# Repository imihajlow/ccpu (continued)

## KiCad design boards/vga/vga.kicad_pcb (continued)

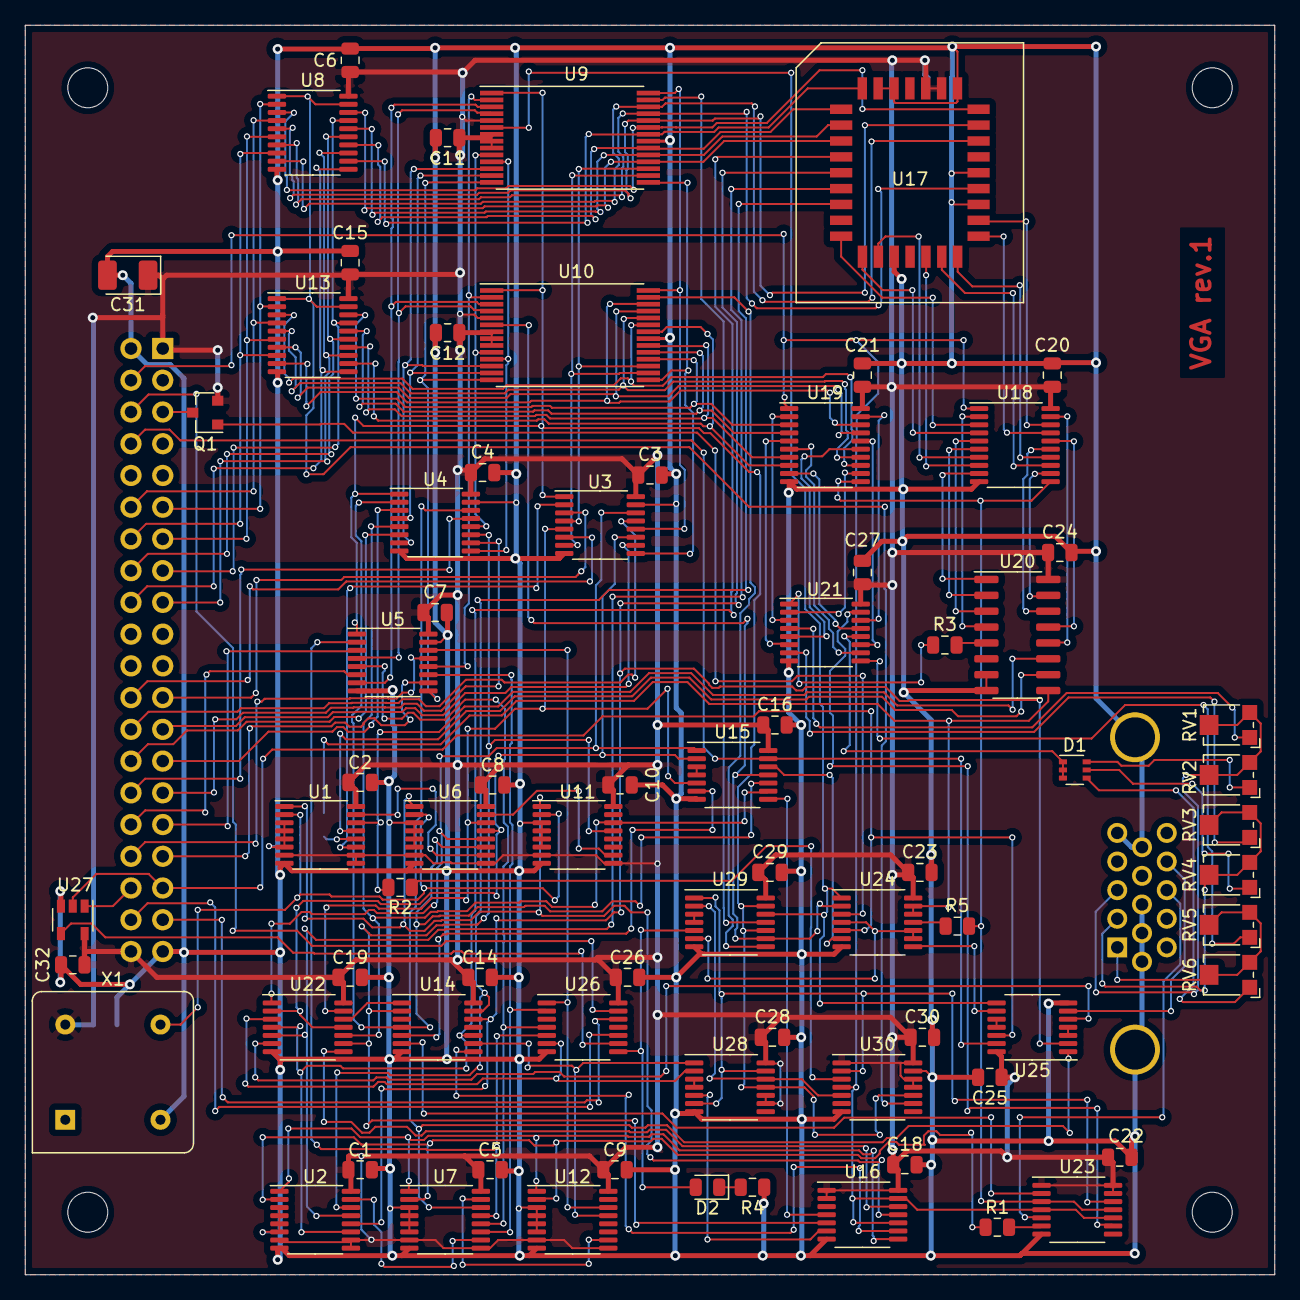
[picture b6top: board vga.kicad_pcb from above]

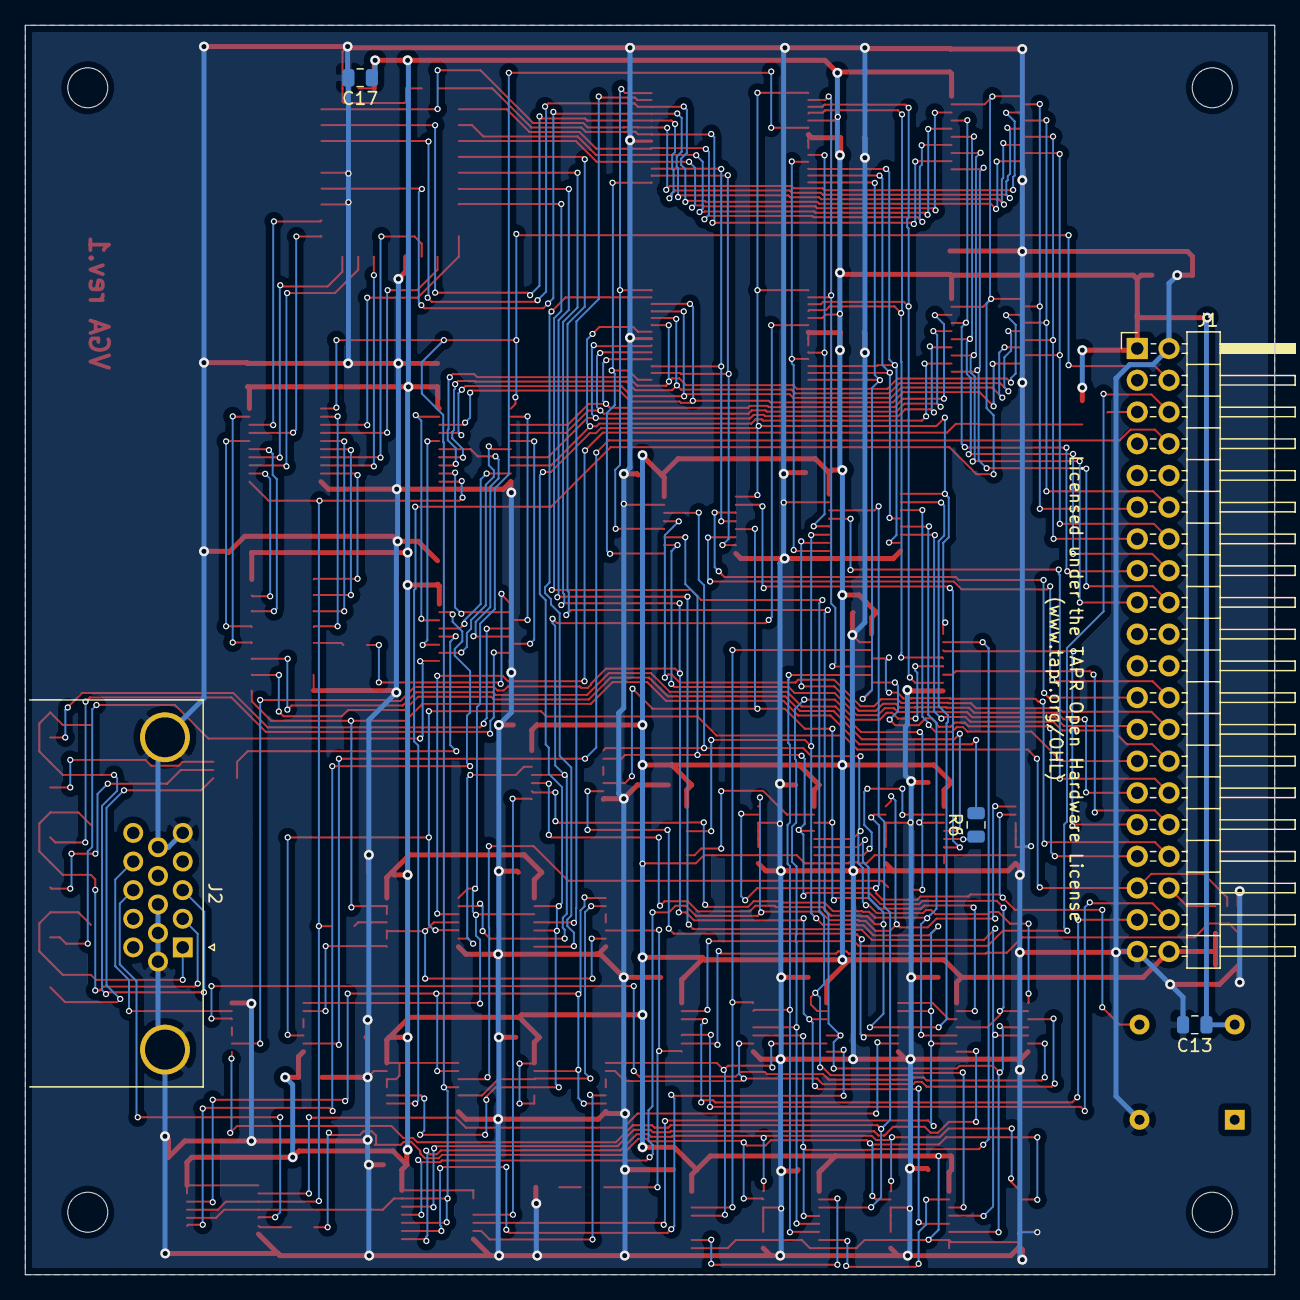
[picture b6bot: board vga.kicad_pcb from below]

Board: 2 copper layers, 100.0 x 100.0 mm, 84 parts (5 on the bottom side), 159 nets.

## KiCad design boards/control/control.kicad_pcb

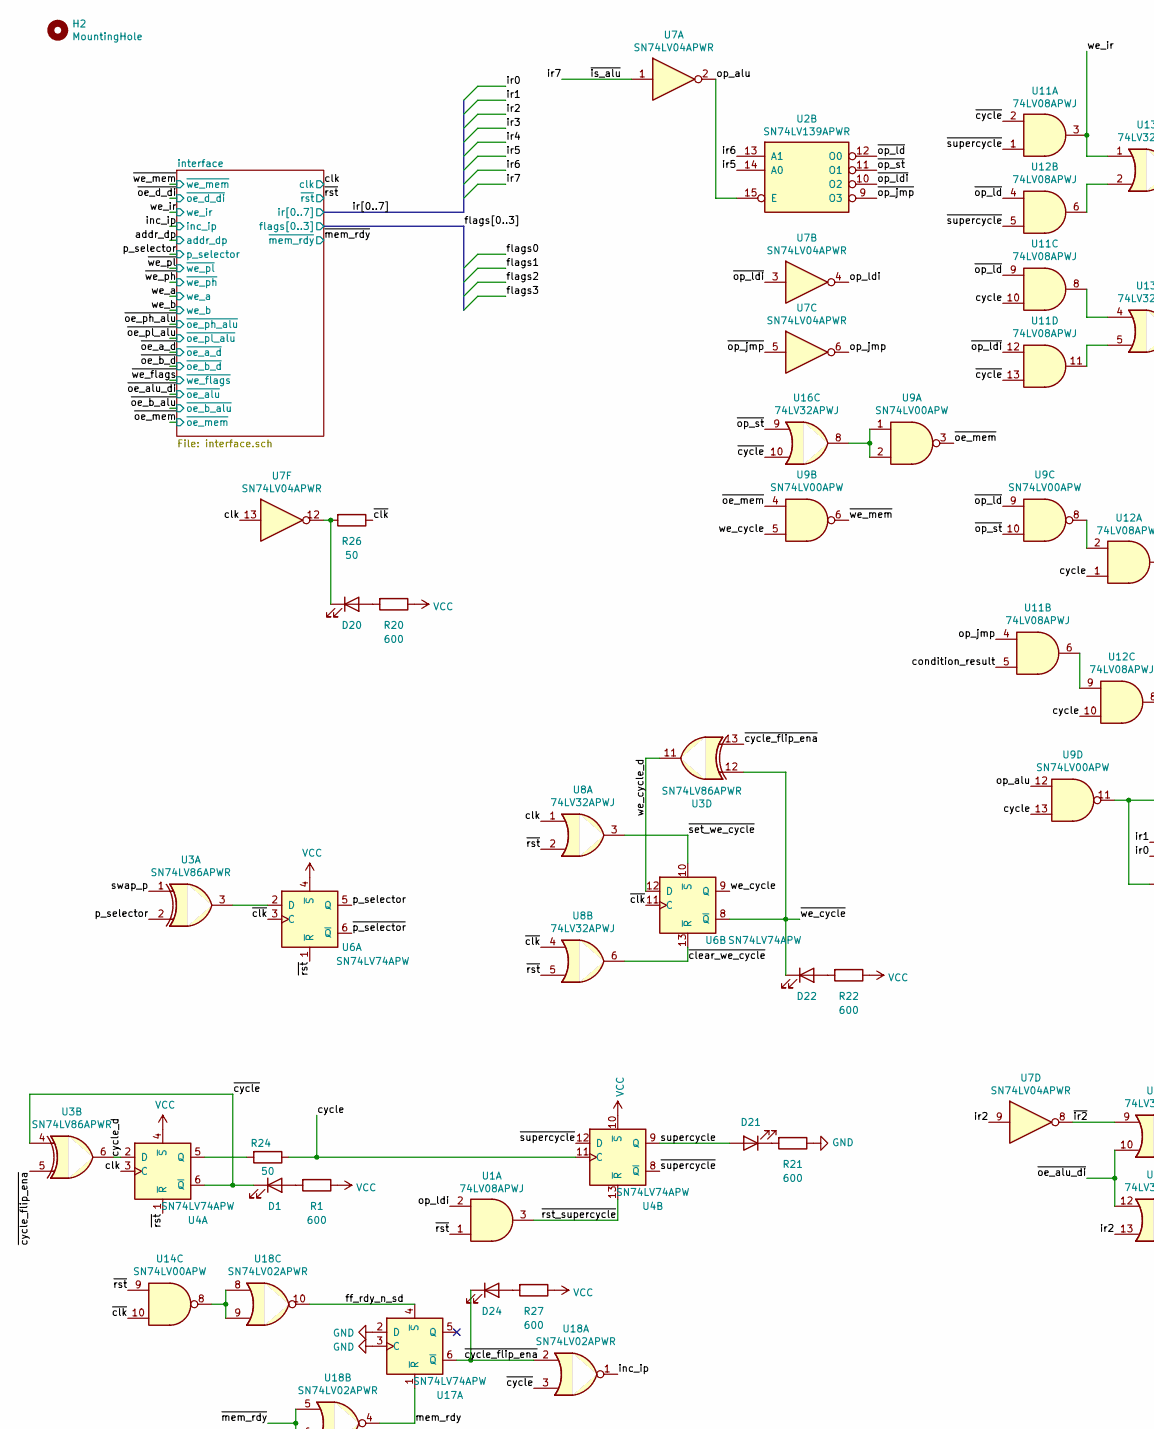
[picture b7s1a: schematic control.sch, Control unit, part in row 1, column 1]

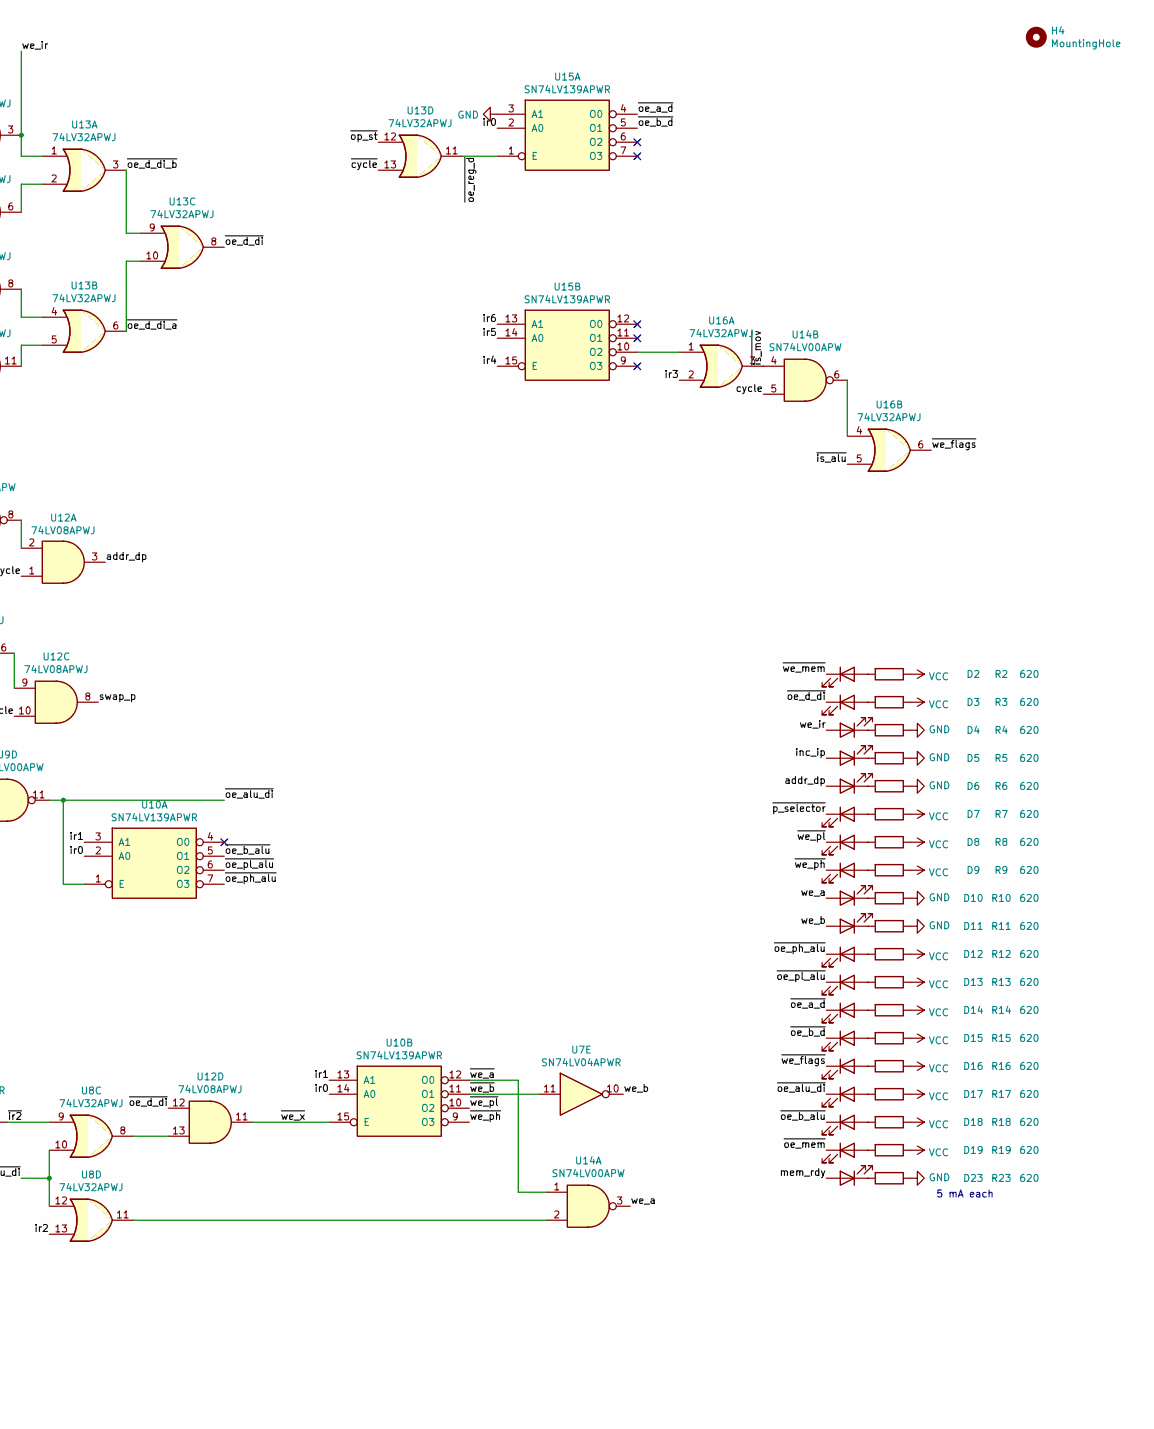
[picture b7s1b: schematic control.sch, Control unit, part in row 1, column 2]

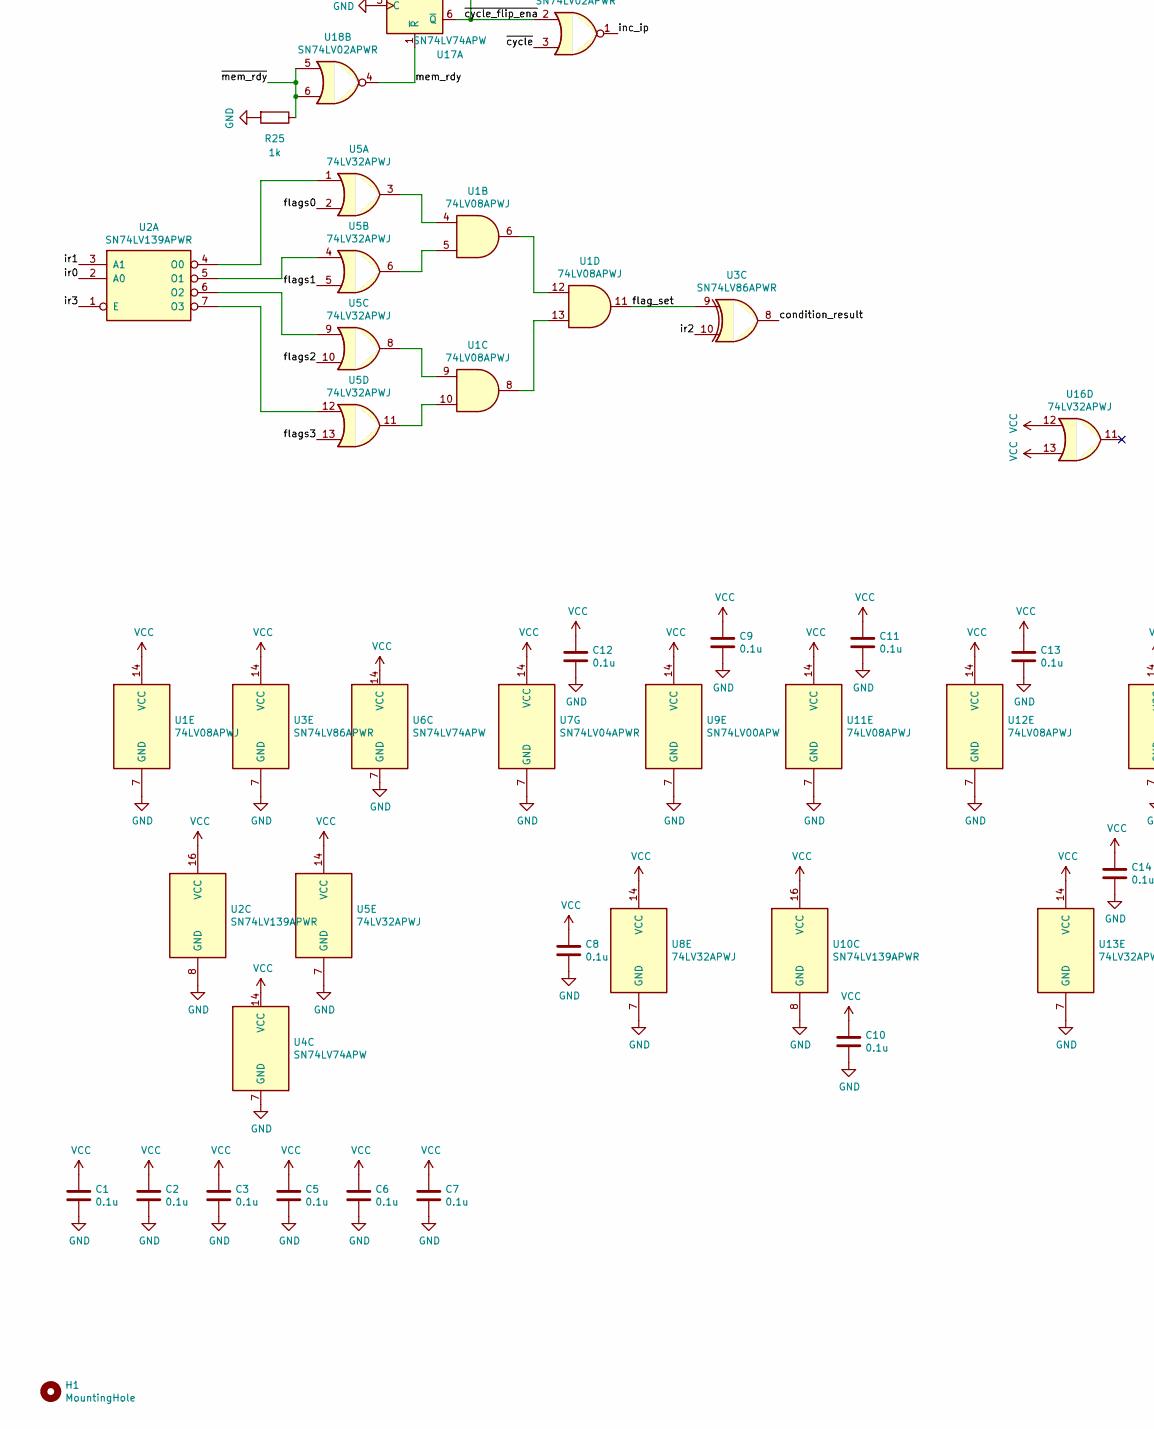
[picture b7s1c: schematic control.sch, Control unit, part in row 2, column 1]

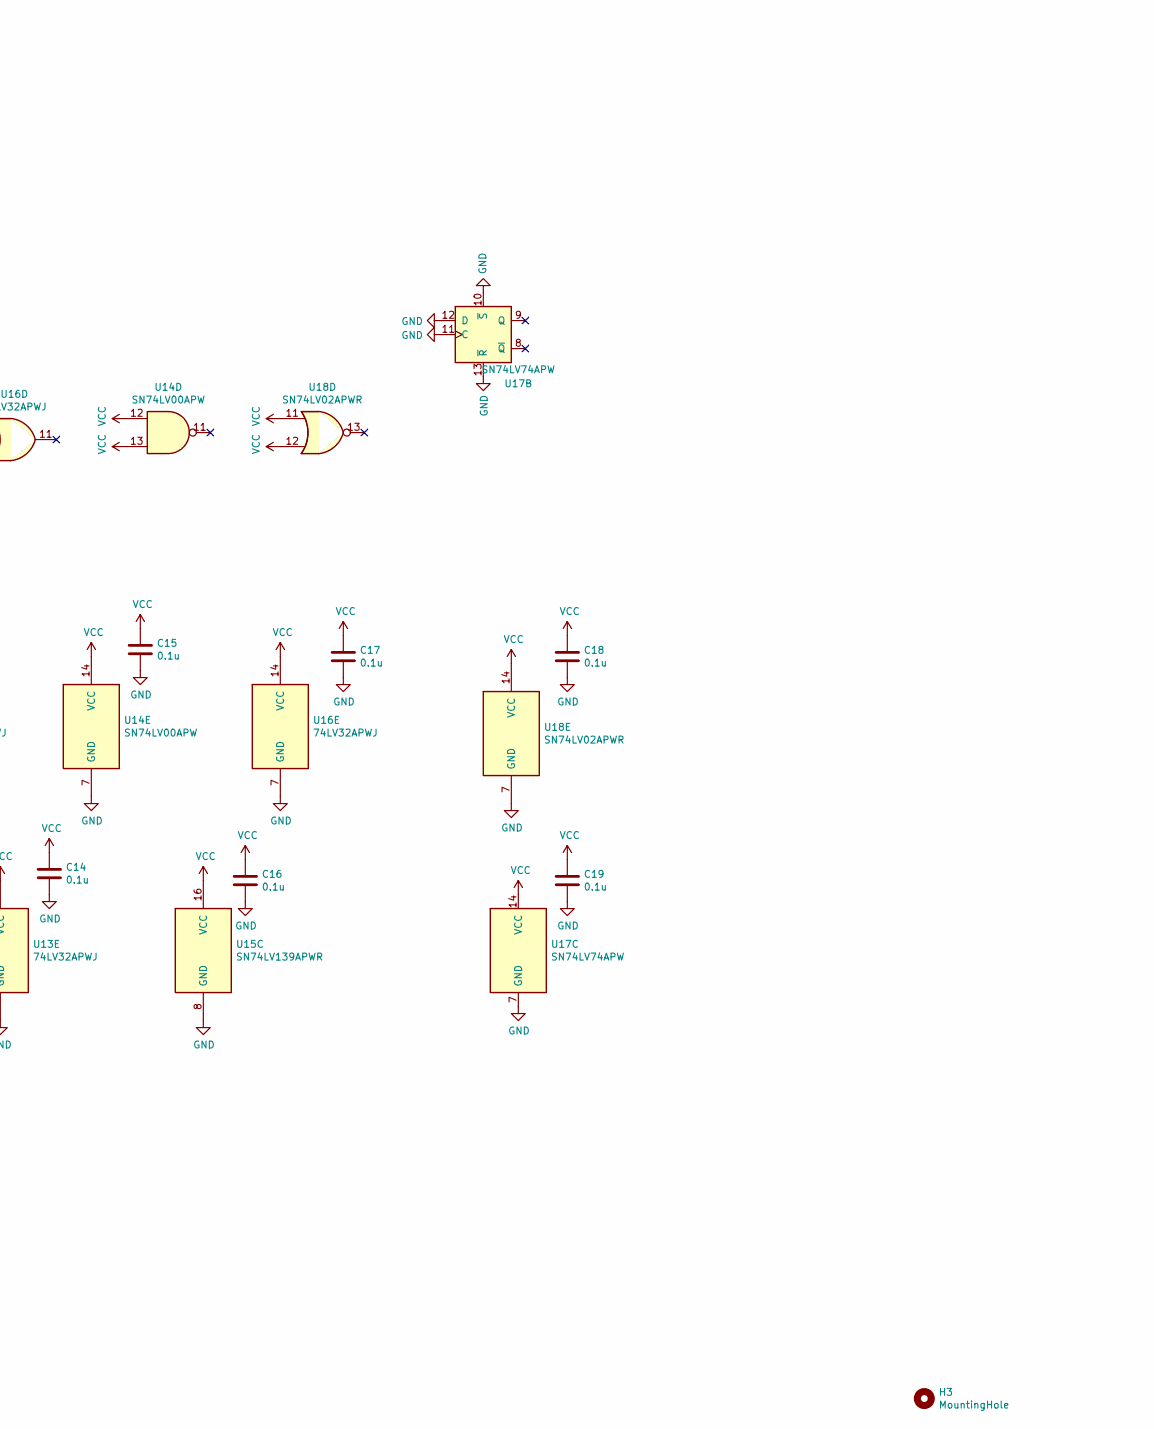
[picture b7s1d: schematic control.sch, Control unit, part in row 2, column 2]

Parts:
C1, C2, C3, C5, C6, C7, C8, C9, C10, C11, C12, C13, C14, C15, C16, C17, C18, C19: 0.1u; C_0805_2012Metric
D1, D20, D21, D22, D24: KP-2012CGCK; LED_0805_2012Metric
D2, D3, D4, D5, D6, D7, D8, D9, D10, D11, D12, D13, D14, D15, D16, D17, D18, D19, D23: KP-2012EC; LED_0805_2012Metric
H1, H2, H3, H4: MountingHole; MountingHole_3.2mm_M3
R1, R20, R21, R22, R27: 600; R_0805_2012Metric
R2, R3, R4, R5, R6, R7, R8, R9, R10, R11, R12, R13, R14, R15, R16, R17, R18, R19, R23: 620; R_0805_2012Metric
R24, R26: 50; R_0805_2012Metric
R25: 1k; R_0805_2012Metric
U1, U11, U12: 74LV08APWJ; TSSOP-14_4.4x5mm_P0.65mm
U2, U10, U15: SN74LV139APWR; TSSOP-16_4.4x5mm_P0.65mm
U3: SN74LV86APWR; TSSOP-14_4.4x5mm_P0.65mm
U4, U6, U17: SN74LV74APW; TSSOP-14_4.4x5mm_P0.65mm
U5, U8, U13, U16: 74LV32APWJ; TSSOP-14_4.4x5mm_P0.65mm
U7: SN74LV04APWR; TSSOP-14_4.4x5mm_P0.65mm
U9, U14: SN74LV00APW; TSSOP-14_4.4x5mm_P0.65mm
U18: SN74LV02APWR; TSSOP-14_4.4x5mm_P0.65mm

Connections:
/addr_dp: D6.2 (A), U12.3; also elsewhere on the board
/clk: U4.3 (C), U7.13, U8.1; also elsewhere on the board
/condition_result: U3.8, U11.5
/cycle: R24.1, U4.11 (C), U9.13, U11.10, U12.1, U12.10, U14.5
/cycle_d: U3.6, U4.2 (D)
/ff_rdy_n_sd: U17.4 (~S), U18.10
/flag_set: U1.11, U3.9
/flags0: U5.2; also elsewhere on the board
/flags1: U5.5; also elsewhere on the board
/flags2: U5.10; also elsewhere on the board
/flags3: U5.13; also elsewhere on the board
/inc_ip: D5.2 (A), U18.1; also elsewhere on the board
/ir0: U2.2 (A0), U10.2 (A0), U10.14 (A0), U15.2 (A0); also elsewhere on the board
/ir1: U2.3 (A1), U10.3 (A1), U10.13 (A1); also elsewhere on the board
/ir2: U3.10, U7.9, U8.13; also elsewhere on the board
/ir3: U2.1 (E), U16.2; also elsewhere on the board
/ir4: U15.15 (E); also elsewhere on the board
/ir5: U2.14 (A0), U15.14 (A0); also elsewhere on the board
/ir6: U2.13 (A1), U15.13 (A1); also elsewhere on the board
/ir7: U7.1, U16.5; also elsewhere on the board
/mem_rdy: D23.2 (A), U17.1 (~R), U18.4
/op_alu: U2.15 (E), U7.2, U9.12
/op_jmp: U7.6, U11.4
/op_ldi: U1.2, U7.4
/p_selector: U3.2, U6.5 (Q); also elsewhere on the board
/supercycle: D21.2 (A), U4.9 (Q)
/swap_p: U3.1, U12.8
/we_a: D10.2 (A), U14.3; also elsewhere on the board
/we_b: D11.2 (A), U7.10; also elsewhere on the board
/we_cycle: U6.9 (Q), U9.5
/we_cycle_d: U3.11, U6.12 (D)
/we_ir: D4.2 (A), U11.3, U13.1; also elsewhere on the board
/~clear_we_cycle: U6.13 (~R), U8.6
/~clk: R26.1, U6.3 (C), U6.11 (C), U8.4, U14.10
/~cycle: D1.1 (K), U3.4, U4.6 (~Q), U11.2, U11.13, U13.13, U16.10, U18.3
/~cycle_flip_ena: D24.1 (K), U3.5, U3.13, U17.6 (~Q), U18.2
/~ir2: U7.8, U8.9
/~is_mov: U14.4, U16.3
/~mem_rdy: R25.1, U18.5, U18.6; also elsewhere on the board
/~oe_a_d: D14.1 (K), U15.4 (O0); also elsewhere on the board
/~oe_alu_di: D17.1 (K), U8.10, U8.12, U9.11, U10.1 (E); also elsewhere on the board
/~oe_b_alu: D18.1 (K), U10.5 (O1); also elsewhere on the board
/~oe_b_d: D15.1 (K), U15.5 (O1); also elsewhere on the board
/~oe_d_di: D3.1 (K), U12.12, U13.8; also elsewhere on the board
/~oe_d_di_a: U13.6, U13.10
/~oe_d_di_b: U13.3, U13.9
/~oe_mem: D19.1 (K), U9.3, U9.4; also elsewhere on the board
/~oe_ph_alu: D12.1 (K), U10.7 (O3); also elsewhere on the board
/~oe_pl_alu: D13.1 (K), U10.6 (O2); also elsewhere on the board
/~oe_reg_d: U13.11, U15.1 (E)
/~op_jmp: U2.9 (O3), U7.5
/~op_ld: U2.12 (O0), U9.9, U11.9, U12.4
/~op_ldi: U2.10 (O2), U7.3, U11.12
/~op_st: U2.11 (O1), U9.10, U13.12, U16.9
/~p_selector: D7.1 (K), U6.6 (~Q)
/~rst: U1.1, U4.1 (~R), U6.1 (~R), U8.2, U8.5, U14.9; also elsewhere on the board
/~rst_supercycle: U1.3, U4.13 (~R)
/~set_we_cycle: U6.10 (~S), U8.3
/~supercycle: U4.8 (~Q), U4.12 (D), U11.1, U12.5
/~we_a: U10.12 (O0), U14.1
/~we_b: U7.11, U10.11 (O1)
/~we_cycle: D22.1 (K), U3.12, U6.8 (~Q)
/~we_flags: D16.1 (K), U16.6; also elsewhere on the board
/~we_mem: D2.1 (K), U9.6; also elsewhere on the board
/~we_ph: D9.1 (K), U10.9 (O3); also elsewhere on the board
/~we_pl: D8.1 (K), U10.10 (O2); also elsewhere on the board
/~we_x: U10.15 (E), U12.11
GND: C1.2, C2.2, C3.2, C5.2, C6.2, C7.2, C8.2, C9.2, C10.2, C11.2, C12.2, C13.2, C14.2, C15.2, C16.2, C17.2, C18.2, C19.2, R4.1, R5.1, R6.1, R10.1, R11.1, R21.1, R23.1, R25.2, U1.7 (GND), U2.8 (GND), U3.7 (GND), U4.7 (GND), U5.7 (GND), U6.7 (GND), U7.7 (GND), U8.7 (GND), U9.7 (GND), U10.8 (GND), U11.7 (GND), U12.7 (GND), U13.7 (GND), U14.7 (GND), U15.3 (A1), U15.8 (GND), U16.7 (GND), U17.2 (D), U17.3 (C), U17.7 (GND), U17.10 (~S), U17.11 (C), U17.12 (D), U17.13 (~R), U18.7 (GND); also elsewhere on the board
unnamed: D1.2 (A), R1.2
unnamed: D2.2 (A), R2.2
unnamed: D3.2 (A), R3.2
unnamed: D4.1 (K), R4.2
unnamed: D5.1 (K), R5.2
unnamed: D6.1 (K), R6.2
unnamed: D7.2 (A), R7.2
unnamed: D8.2 (A), R8.2
unnamed: D9.2 (A), R9.2
unnamed: D10.1 (K), R10.2
unnamed: D11.1 (K), R11.2
unnamed: D12.2 (A), R12.2
unnamed: D13.2 (A), R13.2
unnamed: D14.2 (A), R14.2
unnamed: D15.2 (A), R15.2
unnamed: D16.2 (A), R16.2
unnamed: D17.2 (A), R17.2
unnamed: D18.2 (A), R18.2
unnamed: D19.2 (A), R19.2
unnamed: D20.1 (K), R26.2, U7.12
unnamed: D20.2 (A), R20.2
unnamed: D21.1 (K), R21.2
unnamed: D22.2 (A), R22.2
unnamed: D23.1 (K), R23.2
unnamed: D24.2 (A), R27.2
unnamed: R24.2, U4.5 (Q)
unnamed: U1.4, U5.3
unnamed: U1.5, U5.6
unnamed: U1.9, U5.8
unnamed: U1.10, U5.11
unnamed: U1.6, U1.12
unnamed: U1.8, U1.13
unnamed: U2.4 (O0), U5.1
unnamed: U2.5 (O1), U5.4
unnamed: U2.6 (O2), U5.9
unnamed: U2.7 (O3), U5.12
unnamed: U3.3, U6.2 (D)
unnamed: U11.6, U12.9
unnamed: U11.8, U13.4
unnamed: U11.11, U13.5
unnamed: U9.8, U12.2
unnamed: U12.6, U13.2
unnamed: U8.8, U12.13
unnamed: U8.11, U14.2
unnamed: U14.6, U16.4
unnamed: U14.8, U18.8, U18.9
unnamed: U15.10 (O2), U16.1
unnamed: U9.1, U9.2, U16.8
VCC: C1.1, C2.1, C3.1, C5.1, C6.1, C7.1, C8.1, C9.1, C10.1, C11.1, C12.1, C13.1, C14.1, C15.1, C16.1, C17.1, C18.1, C19.1, R1.1, R2.1, R3.1, R7.1, R8.1, R9.1, R12.1, R13.1, R14.1, R15.1, R16.1, R17.1, R18.1, R19.1, R20.1, R22.1, R27.1, U1.14 (VCC), U2.16 (VCC), U3.14 (VCC), U4.4 (~S), U4.10 (~S), U4.14 (VCC), U5.14 (VCC), U6.4 (~S), U6.14 (VCC), U7.14 (VCC), U8.14 (VCC), U9.14 (VCC), U10.16 (VCC), U11.14 (VCC), U12.14 (VCC), U13.14 (VCC), U14.12, U14.13, U14.14 (VCC), U15.16 (VCC), U16.12, U16.13, U16.14 (VCC), U17.14 (VCC), U18.11, U18.12, U18.14 (VCC); also elsewhere on the board

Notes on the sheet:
5 mA each

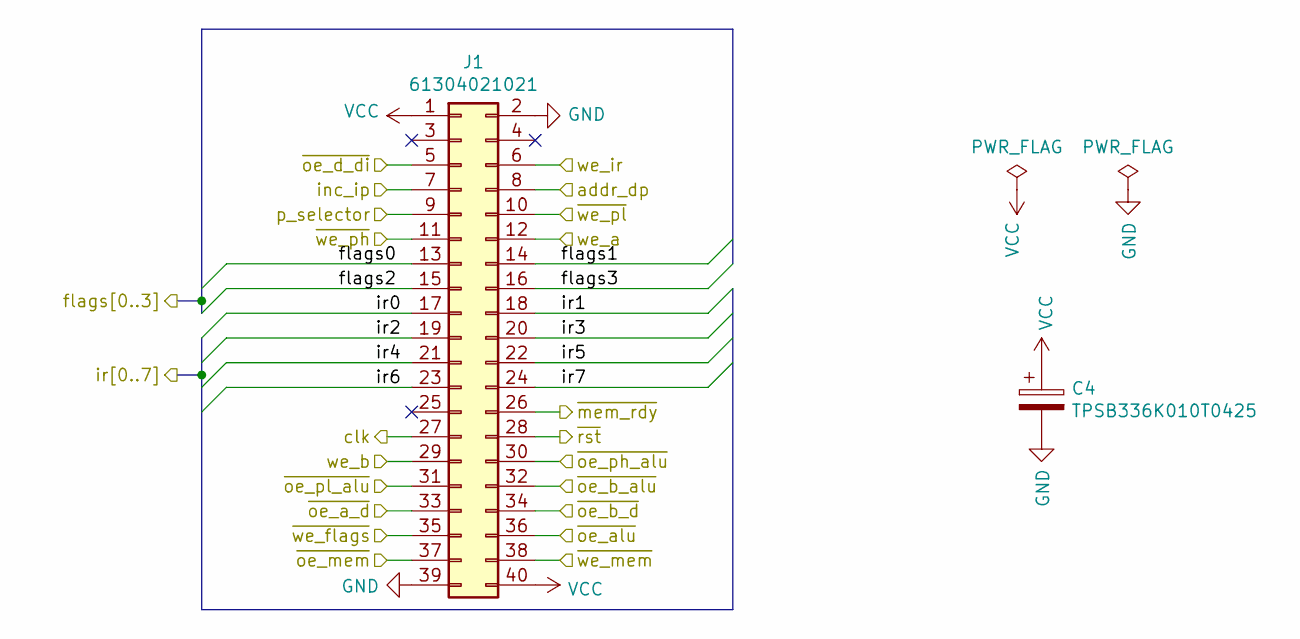
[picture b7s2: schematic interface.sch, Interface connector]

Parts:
C4: TPSB336K010T0425; CP_EIA-3528-21_Kemet-B_Pad1.50x2.35mm_HandSolder
J1: 61304021021; PinHeader_2x20_P2.54mm_Horizontal

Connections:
/addr_dp: J1.8; also elsewhere on the board
/clk: J1.27; also elsewhere on the board
/flags0: J1.13; also elsewhere on the board
/flags1: J1.14; also elsewhere on the board
/flags2: J1.15; also elsewhere on the board
/flags3: J1.16; also elsewhere on the board
/inc_ip: J1.7; also elsewhere on the board
/ir0: J1.17; also elsewhere on the board
/ir1: J1.18; also elsewhere on the board
/ir2: J1.19; also elsewhere on the board
/ir3: J1.20; also elsewhere on the board
/ir4: J1.21; also elsewhere on the board
/ir5: J1.22; also elsewhere on the board
/ir6: J1.23; also elsewhere on the board
/ir7: J1.24; also elsewhere on the board
/p_selector: J1.9; also elsewhere on the board
/we_a: J1.12; also elsewhere on the board
/we_b: J1.29; also elsewhere on the board
/we_ir: J1.6; also elsewhere on the board
/~mem_rdy: J1.26; also elsewhere on the board
/~oe_a_d: J1.33; also elsewhere on the board
/~oe_alu_di: J1.36; also elsewhere on the board
/~oe_b_alu: J1.32; also elsewhere on the board
/~oe_b_d: J1.34; also elsewhere on the board
/~oe_d_di: J1.5; also elsewhere on the board
/~oe_mem: J1.37; also elsewhere on the board
/~oe_ph_alu: J1.30; also elsewhere on the board
/~oe_pl_alu: J1.31; also elsewhere on the board
/~rst: J1.28; also elsewhere on the board
/~we_flags: J1.35; also elsewhere on the board
/~we_mem: J1.38; also elsewhere on the board
/~we_ph: J1.11; also elsewhere on the board
/~we_pl: J1.10; also elsewhere on the board
GND: C4.2, J1.2, J1.39; also elsewhere on the board
VCC: C4.1, J1.1, J1.40; also elsewhere on the board

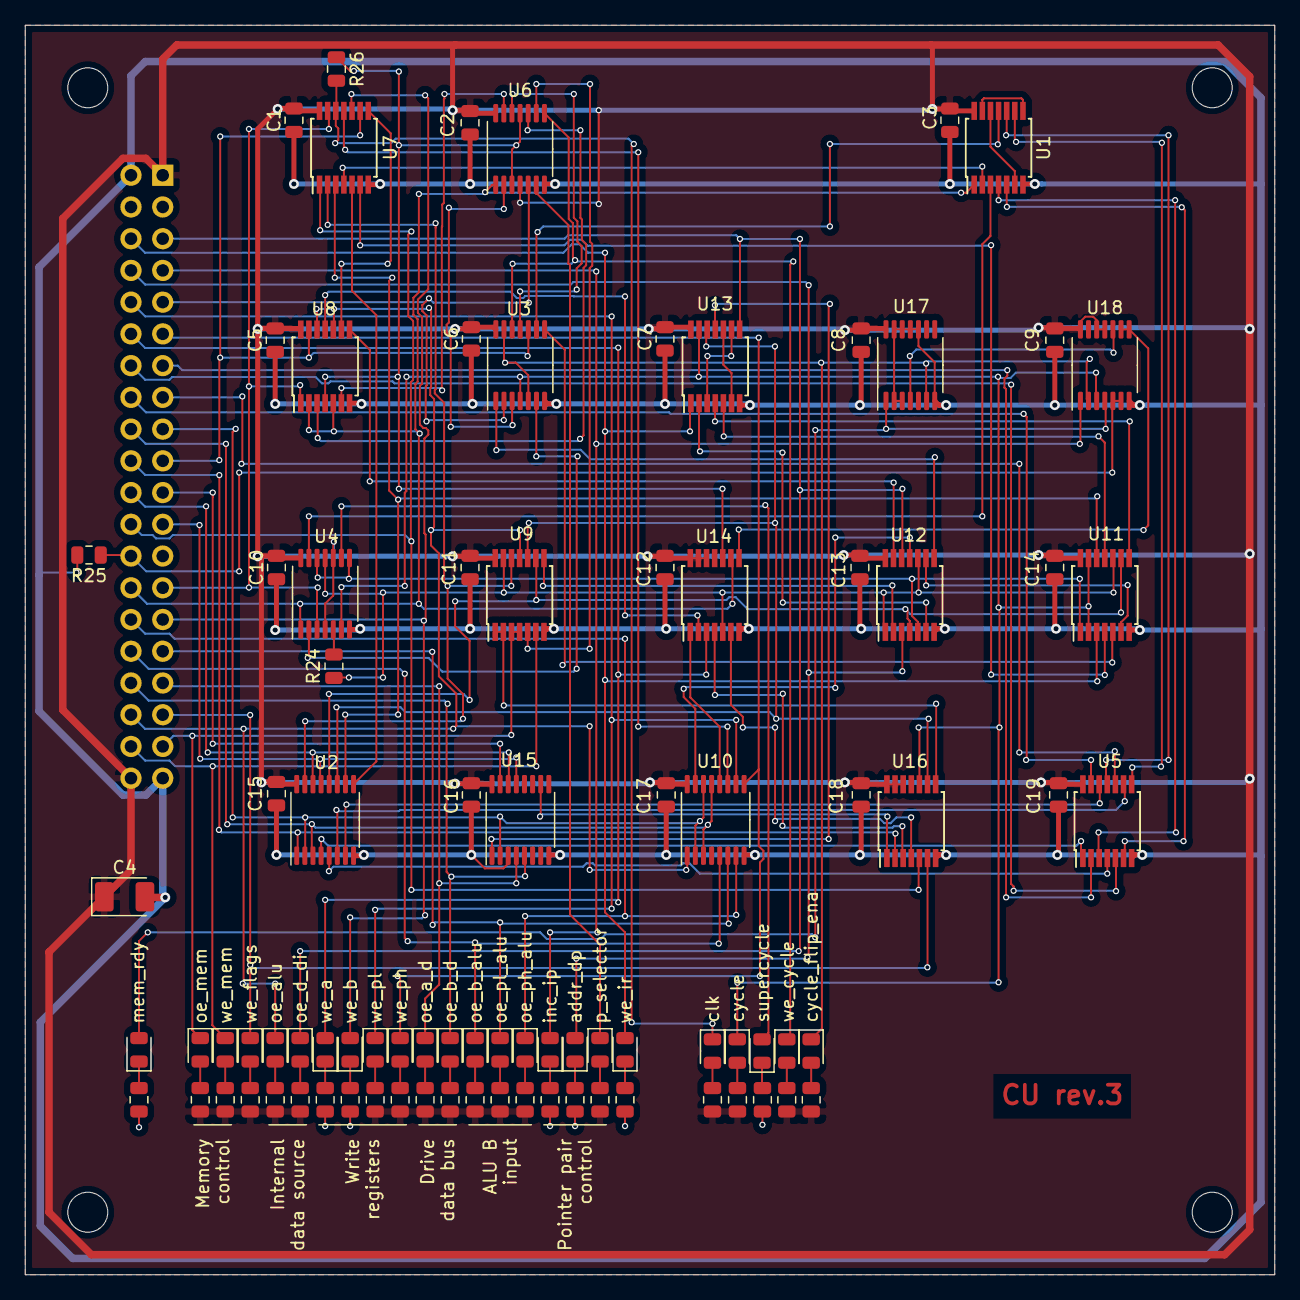
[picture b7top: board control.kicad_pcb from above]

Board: 2 copper layers, 100.0 x 100.0 mm, 93 parts (1 on the bottom side), 117 nets.
